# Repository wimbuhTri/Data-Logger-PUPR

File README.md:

# Data-Logger
 Project dari PUPR

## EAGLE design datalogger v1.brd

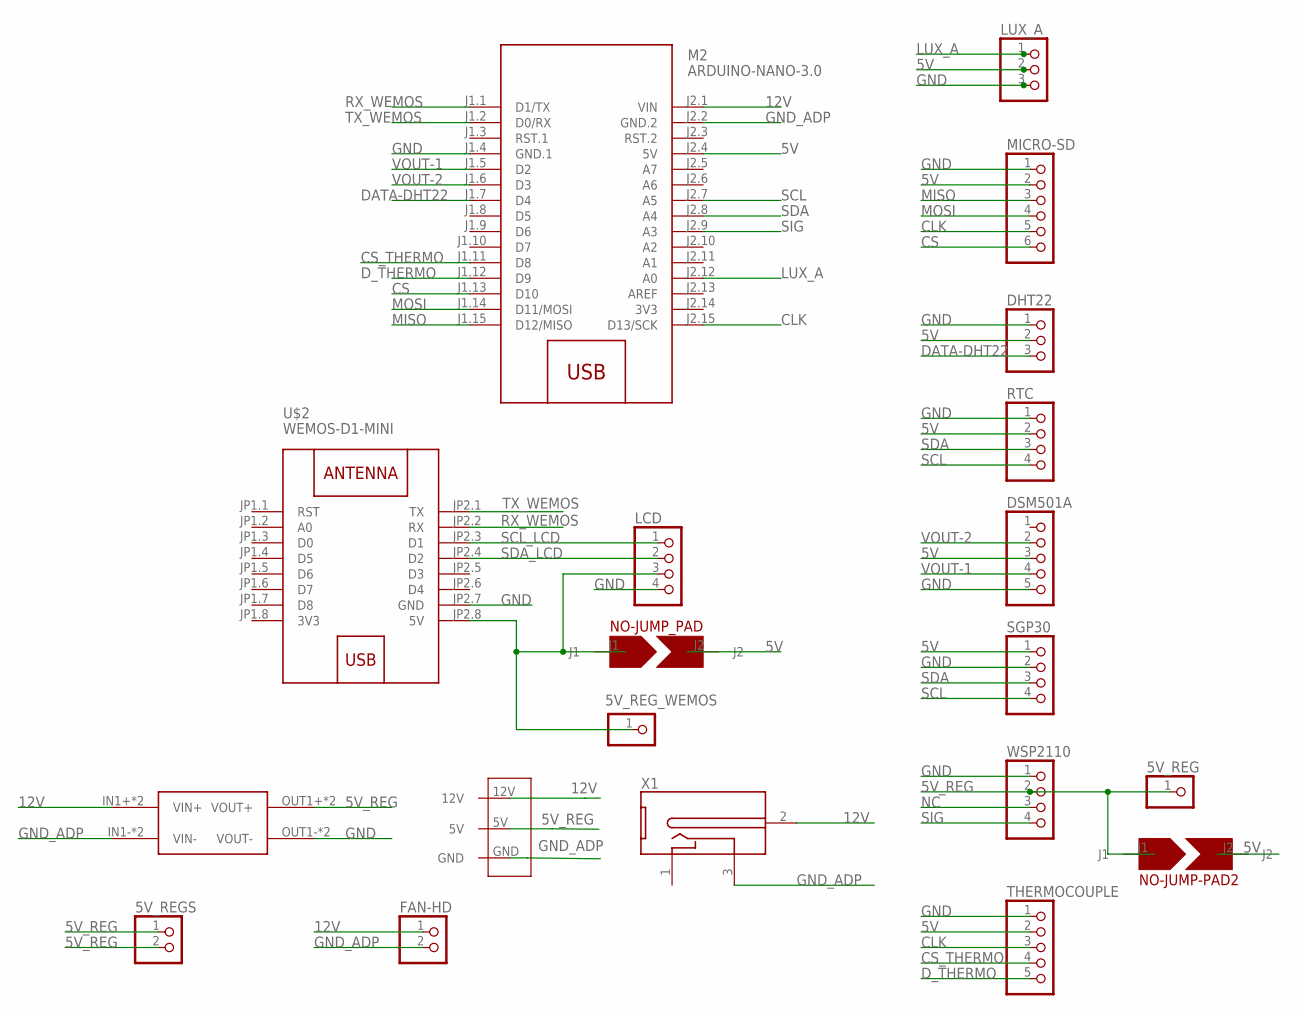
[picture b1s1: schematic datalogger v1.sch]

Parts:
5V_REG, 5V_REG_WEMOS: PINHD-1X1; 1X01
5V_REGS: PINHD-1X2; 1X02
DHT22: PINHD-1X3; 1X03
DSM501A: PINHD-1X5; 1X05
FAN-HD: PINHD-1X2; 1X02
LCD: PINHD-1X4; 1X04
LUX_A: PINHD-1X3; 1X03
M2: ARDUINO-NANO-3.0
MICRO-SD: PINHD-1X6; 1X06
NO-JUMP-PAD2: JUMP-NO; JOMP-NO
NO-JUMP_PAD: JUMP-NO; JOMP-NO
RTC: PINHD-1X4; 1X04
SGP30: PINHD-1X4; 1X04
THERMOCOUPLE: PINHD-1X5; 1X05
U$1: MP1584; DC-BRICK
U$2: WEMOS-D1-MINI
U$3: EDGE_CONNECTOR
WSP2110: PINHD-1X4; 1X04
X1: DC-2.1MM-5MM; DC-21MM

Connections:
1: X1.1
3V3: M2.J2.14 (3V3), U$2.JP1.8 (3V3)
5V: DHT22.2, DSM501A.3, LUX_A.2, M2.J2.4 (5V), MICRO-SD.2, NO-JUMP-PAD2.J2, NO-JUMP_PAD.J2, RTC.2, SGP30.1, THERMOCOUPLE.2
5V_REG: 5V_REG.1, 5V_REGS.1, 5V_REGS.2, NO-JUMP-PAD2.J1, U$1.OUT1+ (VOUT+), U$1.OUT2+ (VOUT+), U$3.5V, WSP2110.2
12V: FAN-HD.1, M2.J2.1 (VIN), U$1.IN1+ (VIN+), U$1.IN2+ (VIN+), U$3.12V, X1.2 (3)
CLK: M2.J2.15 (D13/SCK), MICRO-SD.5, THERMOCOUPLE.3
CS: M2.J1.13 (D10), MICRO-SD.6
CS_THERMO: M2.J1.11 (D8), THERMOCOUPLE.4
DATA-DHT22: DHT22.3, M2.J1.7 (D4)
D_THERMO: M2.J1.12 (D9), THERMOCOUPLE.5
GND: DHT22.1, DSM501A.5, LCD.4, LUX_A.3, M2.J1.4 (GND.1), MICRO-SD.1, RTC.1, SGP30.2, THERMOCOUPLE.1, U$1.OUT1- (VOUT-), U$1.OUT2- (VOUT-), U$2.JP2.7 (GND), WSP2110.1
GND_ADP: FAN-HD.2, M2.J2.2 (GND.2), U$1.IN1- (VIN-), U$1.IN2- (VIN-), U$3.GND, X1.3 (2)
LUX_A: LUX_A.1, M2.J2.12 (A0)
MISO: M2.J1.15 (D12/MISO), MICRO-SD.3
MOSI: M2.J1.14 (D11/MOSI), MICRO-SD.4
unnamed: 5V_REG_WEMOS.1, LCD.3, NO-JUMP_PAD.J1, U$2.JP2.8 (5V)
NC: WSP2110.3
RX_WEMOS: M2.J1.1 (D1/TX), U$2.JP2.2 (RX)
SCL: M2.J2.7 (A5), RTC.4, SGP30.4
SCL_LCD: LCD.1, U$2.JP2.3 (D1)
SDA: M2.J2.8 (A4), RTC.3, SGP30.3
SDA_LCD: LCD.2, U$2.JP2.4 (D2)
SIG: M2.J2.9 (A3), WSP2110.4
TX_WEMOS: M2.J1.2 (D0/RX), U$2.JP2.1 (TX)
VOUT-1: DSM501A.4, M2.J1.5 (D2)
VOUT-2: DSM501A.2, M2.J1.6 (D3)

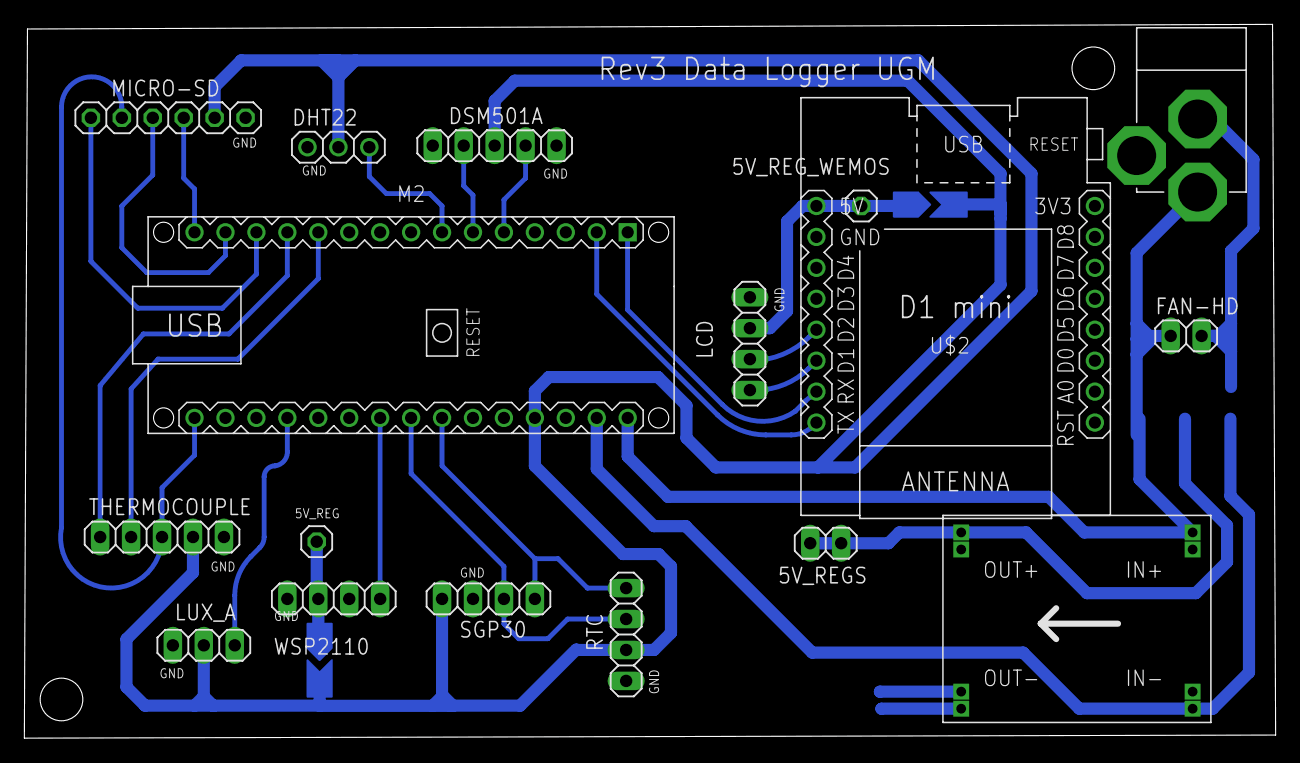
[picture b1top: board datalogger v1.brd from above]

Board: 2 copper layers, 102.7 x 58.6 mm, 20 parts (0 on the bottom side), 24 nets.

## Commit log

2021-12-15 final
2021-12-15 move to forder
2021-12-21 update board
2021-12-24 rev stl file v4
2021-12-27 update pcb
2021-12-30 add interval gspread update
2021-12-30 temelm no duplocate and ordered

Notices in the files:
parts and their libraries:
diy-modules: Released under the Creative Commons Attribution 4.0 International License: http://creativecommons.org/licenses/by/4.0
